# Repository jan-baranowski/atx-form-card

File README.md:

ATX Form Card
=============

This is the repo containig project files, production files and documentation for an ATX Form Card - USB+IrDA+PS/2 bracket to be used in late AT motherboards produced by PCChips and ASUS ca. 1997.

Complete description of this project can be found at https://patoelektronika.blogspot.com/2024/10/atx-form-card.html

All the work that is not a third party documentation or libraries is licenced under WTFPLv2.

Third-party items incorporated
------------------------------

1. ATX Form Card reverse engineering attempt by Jacek Głogowski - /doc/glogowski.pdf - https://jacek.unixstorm.org/elektronika/atx-form-card.html
2. mini DIN EAGLE library - /hw/atx_from_card/mini_din.lbr - https://forums.parallax.com/discussion/124010/what-is-the-ps2-connectors-name-in-the-eagle-lib
3. polygon version os Open Source Hardware logos library for EAGLE - /hw/atx_from_card/oshw_custom.lbr - Andrew Cooper, http://www.darkerview.com
4. documentation on using HP C4103a IR transceiver with ASUS motherboards - /doc/irda/* - http://www.colin99.co.uk/extras/irda/hp_c4103a_irda.htm and https://www.infrarotport.de/mobo/asus_ir.htm
5. documentation on audio bracket, a companion to ATX Form Card - /doc/25-pin-sound-game-ribbon-cable - https://retrocomputing.stackexchange.com/questions/25069/25-pin-sound-game-ribbon-cable

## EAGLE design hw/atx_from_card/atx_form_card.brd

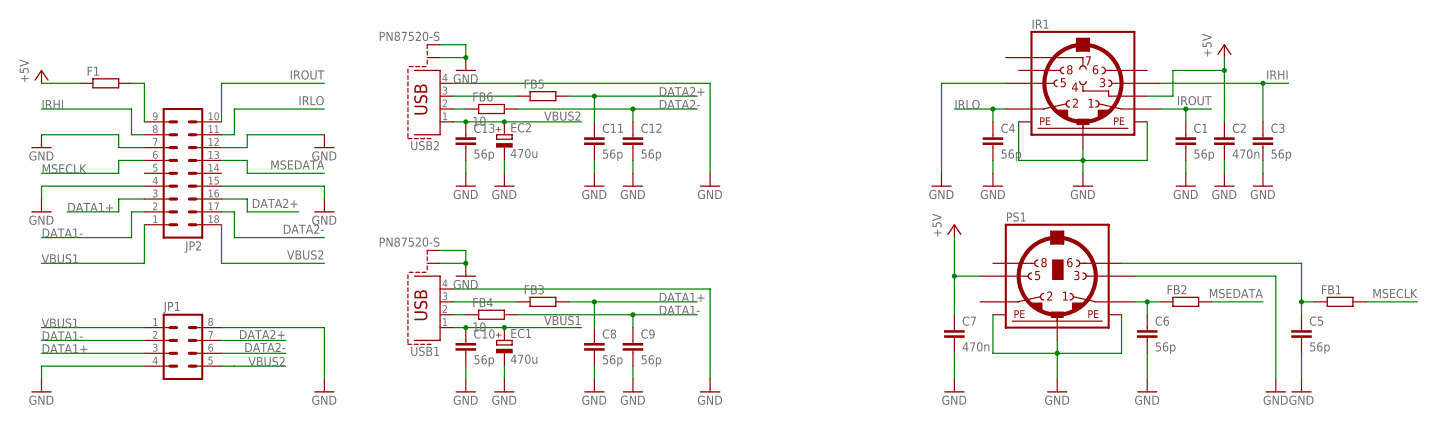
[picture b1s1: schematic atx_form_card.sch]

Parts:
C1, C3, C4, C5, C6, C8, C9, C10, C11, C12, C13: 56p; C3216
C2, C7: 470n; C3216
EC1, EC2: 470u; E3,5-8
F1: R-EU_0207/10; 0207/10
FB1, FB2, FB3, FB5: R-EU_M3216; M3216
FB4, FB6: 10; M3216
IR1: MINI_DIN_8; M_DIN8
JP1: MA04-2
JP2: MA09-2
PS1: MINI_DIN_6; M_DIN6
USB1, USB2: PN87520-S

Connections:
DATA1+: C8.1, FB3.2, JP1.3, JP2.3 (3_)
DATA1-: C9.1, FB4.2, JP1.2, JP2.2 (2_)
DATA2+: C11.1, FB5.2, JP1.7, JP2.16 (12_)
DATA2-: C12.1, FB6.2, JP1.6, JP2.17 (11_)
GND: C1.2, C2.2, C3.2, C4.2, C5.2, C6.2, C7.2, C8.2, C9.2, C10.2, C11.2, C12.2, C13.2, EC1.-, EC2.-, IR1.5, IR1.SH1 (PE1), IR1.SH2 (PE2), IR1.SH3 (PE3), JP1.4, JP1.8, JP2.4 (4_), JP2.7 (7_), JP2.12 (16_), JP2.15 (13_), PS1.3, PS1.SH1 (PE1), PS1.SH2 (PE2), PS1.SH3 (PE3), USB1.4, USB1.S1, USB1.S2, USB2.4, USB2.S1, USB2.S2
IRHI: C3.1, IR1.3, JP2.8 (8_)
IRLO: C4.1, IR1.2, JP2.11 (17_)
IROUT: C1.1, IR1.1, JP2.10 (18_)
MSECLK: FB1.2, JP2.6 (6_)
MSEDATA: FB2.2, JP2.13 (15_)
unnamed: FB4.1, USB1.2
unnamed: C6.1, FB2.1, PS1.1
unnamed: FB6.1, USB2.2
unnamed: FB3.1, USB1.3
unnamed: FB5.1, USB2.3
unnamed: C5.1, FB1.1, PS1.6
unnamed: F1.2, JP2.9 (9_)
VBUS1: C10.1, EC1.+, JP1.1, JP2.1 (1_), USB1.1
VBUS2: C13.1, EC2.+, JP1.5, JP2.18 (10_), USB2.1
VCC: C2.1, C7.1, F1.1, IR1.4, PS1.5

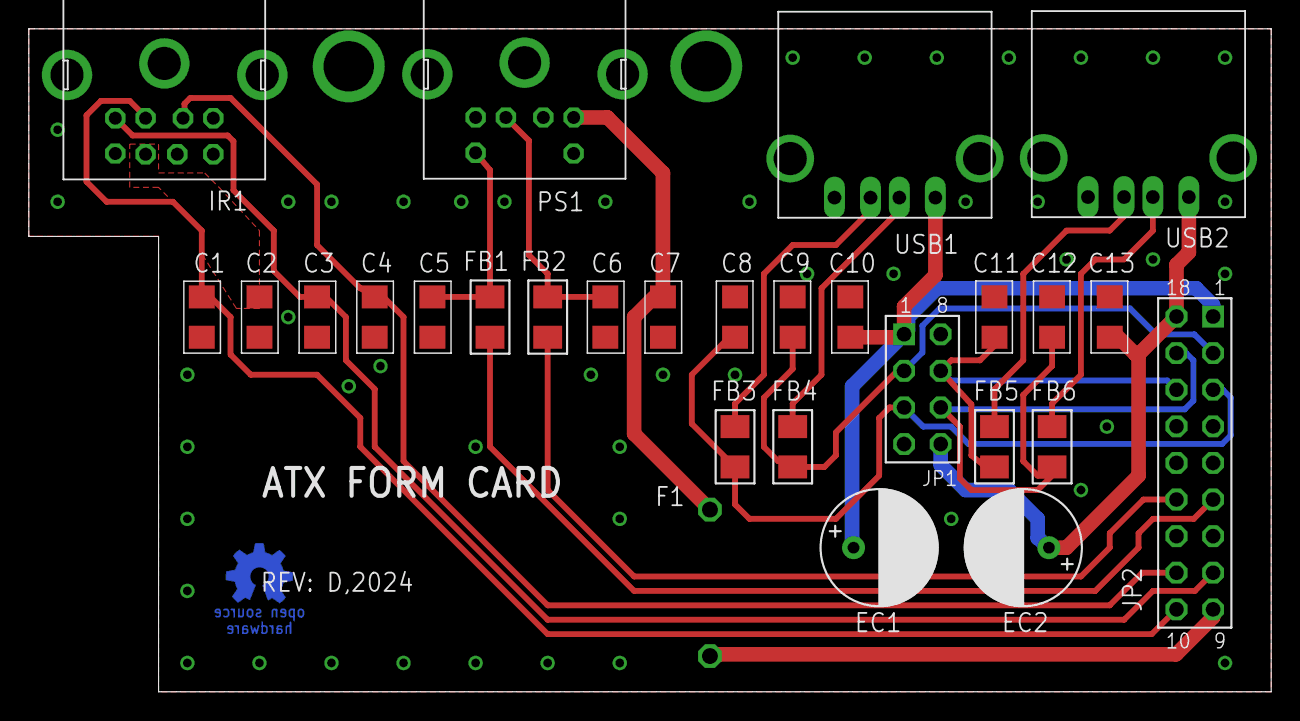
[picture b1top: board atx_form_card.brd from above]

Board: 2 copper layers, 86.2 x 46.0 mm, 29 parts (1 on the bottom side), 20 nets.

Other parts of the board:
U$2: OSHW_5MM

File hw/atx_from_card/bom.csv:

Name;Value;Package;Manufacturer;MPN;
C1;56p 50V 5% C0G;C3216;WALSIN;T-24f190742;
C2;1u 50V X7F;C3216;Samsung;CL31B105KBHNNNE;
C3;56p 50V 5% C0G;C3216;WALSIN;T-24f190742;
C4;56p 50V 5% C0G;C3216;WALSIN;T-24f190742;
C5;56p 50V 5% C0G;C3216;WALSIN;T-24f190742;
C6;56p 50V 5% C0G;C3216;WALSIN;T-24f190742;
C7;1u 50V X7F;C3216;Samsung;CL31B105KBHNNNE;
C8;56p 50V 5% C0G;C3216;WALSIN;T-24f190742;
C9;56p 50V 5% C0G;C3216;WALSIN;T-24f190742;
C10;56p 50V 5% C0G;C3216;WALSIN;T-24f190742;
C11;56p 50V 5% C0G;C3216;WALSIN;T-24f190742;
C12;56p 50V 5% C0G;C3216;WALSIN;T-24f190742;
C13;56p 50V 5% C0G;M3216;WALSIN;T-24f190742;
EC1;470u 10V;E3.5-8;GZZ;T-74627;
EC2;470u 10V;E3.5-8;GZZ;T-74627;
F1;;0207/10;STAR ELECTRONIC/JANTEC;RH356008;
FB1;;M3216;MuRata;BLM31PG601SN1L;
FB2;;M3216;MuRata;BLM31PG601SN1L;
FB3;;M3216;MuRata;BLM31PG601SN1L;
FB4;10;M3216;DRALORIC;D2520010R5%P5;
FB5;;M3216;MuRata;BLM31PG601SN1L;
FB6;10;M3216;DRALORIC;D2520010R5%P5;
IR1;;M_DIN8;TE Connectivity;1658998-1 ;
JP1;not populated;MA04-2;;;
JP2;;MA09-2;;;
PS1;;M_DIN6;TE Connectivity;5749180-1;
USB1;;PN87520-S;Amphenol;87520-0010BLF;
USB2;;PN87520-S;Amphenol;87520-0010BLF;

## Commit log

2024-08-19 Projekt EAGLE
2024-08-19 Dokumentacja źródłowa
2024-08-19 Schemat v1
2024-08-19 Poprawka .gitignore
2024-08-22 Changed lstb library to match pin numeration convention to original. Added additional 4x2 pin USB connector. Changed component numeration to match original. Routed the board. Fixed .gitignore for boa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
2024-09-03 Rev. D of the board. Added more documentation.
2024-09-20 Added gerber files for rev. D
2024-10-09 Renamed some items in third-party documentation.
2024-10-09 Added WTFPLv2 licence.
2024-10-09 Added some readme
2024-10-09 Added some additional documentation on IrDA transceiver to use with ATX Form Card and a companion audio bracket. Updated README.
2024-10-09 Added bill of materials.
2024-10-10 Added current copy of blog article.
